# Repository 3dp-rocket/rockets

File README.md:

# 3D Printed Rockets
The goal of this project is to collaborate on designs of rockets and rocket components for 3D printing.

The first set of designs were developed in [OpenSCAD](https://www.openscad.org/). Using OpenSCAD requires some basic programming skills and it is helpful to have some knowledge of basic math and trigonometry. That said, it is easier to work with existing designs, make tweaks and assemble them into new rockets without knowing any math.

People are encourged to join and add designs they made with other tools. As we learn more togther we will figure out the best tools to use for different projects and skills. 

We want rocket designs to be safe and sound and to follow standard rocket design rules. So we also encourgae contributors to provide documentation about how parts were stress tested and OpenRocket model/simulation results as well as real field test results.

You will find common parts under the 'parts' folder and the first rocket design in this project under 'Janus'. Feel free to add new designs or new parts you have been devloping. Make sure to add a header to your files with you name to get propper attribution. 

To join this project please create an [issue](https://github.com/3dp-rocket/rockets/issues) and type access request in the description. 

Janus - HM115 DM - Tri-Cities - Swoosh - 2019

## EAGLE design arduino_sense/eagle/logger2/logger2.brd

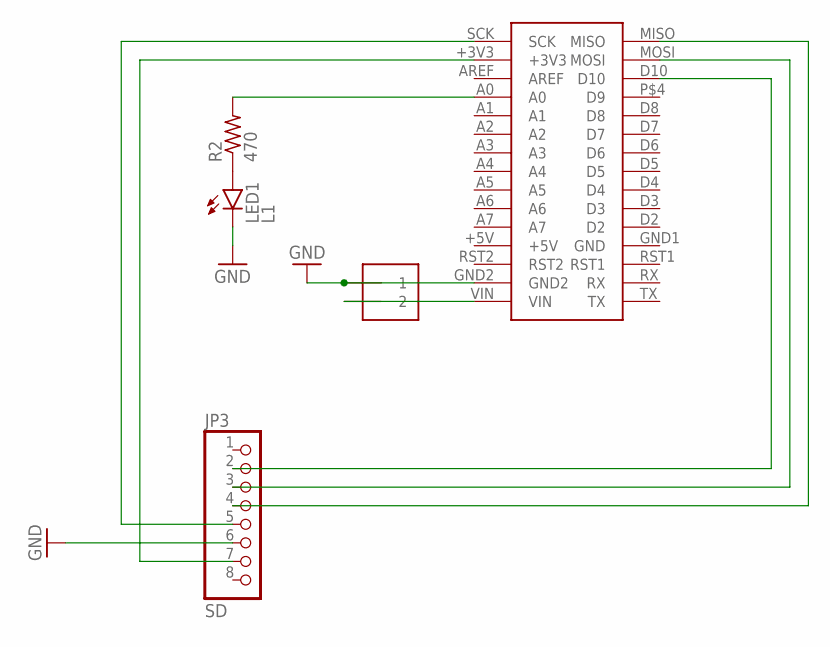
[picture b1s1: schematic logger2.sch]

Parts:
J1: 1X2-3.5MM
JP3: SD; 1X08-BIG
LED1: L1; SFH482
MC1: NANODEVICE; NANO
R2: 470; V526-0

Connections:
GND: J1.1, JP3.6, LED1.K (C), MC1.GND2
unnamed: JP3.5, MC1.SCK
unnamed: JP3.7, MC1.+3V3
unnamed: J1.2, MC1.VIN
unnamed: JP3.3, MC1.MOSI
unnamed: JP3.4, MC1.MISO
unnamed: LED1.A, R2.1
unnamed: JP3.2, MC1.D10
unnamed: MC1.A0, R2.2

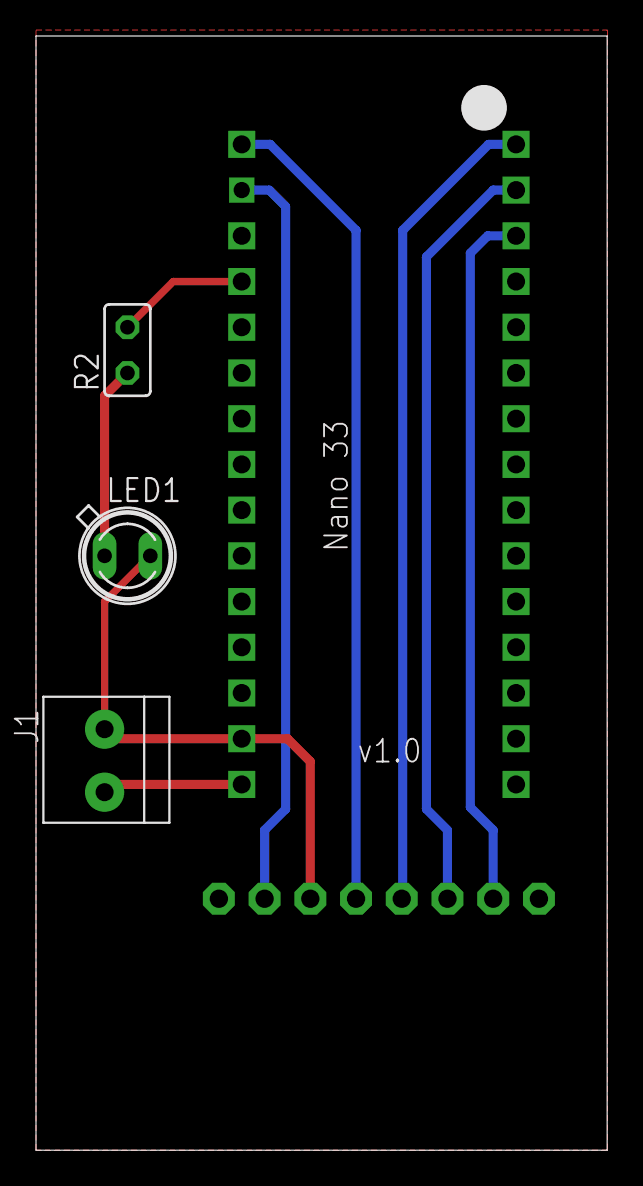
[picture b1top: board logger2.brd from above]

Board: 2 copper layers, 31.7 x 61.9 mm, 5 parts (1 on the bottom side), 9 nets.

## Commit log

2019-05-30 created nose.scad
2019-05-31 created
2019-06-01 janus
2019-06-01 added retainer and lugs
2019-06-01 added janus picture
2019-06-07 added open rocket model
2019-06-13 ellipsoid fin
2019-06-13 thicker fin
2019-06-13 changed fin cord length
2019-06-13 fins
2019-06-15 fixed ring height
2019-09-15 new piston, ejection charge test device
2019-09-29 updated piston
2019-09-29 new build scripts
2019-12-21 preparing to test rocket with 54mm motor
2019-12-21 adding build scripts
2020-01-11 changed threading library to OpenSCAD std library
2020-01-11 updated stl's
2020-01-12 changed motor retainer thread size
2020-01-20 fix fin support gap in motor tube
2020-01-20 track *.stl files using git lfs
2020-01-20 udpated stls
2020-01-23 new ejection charge holder for static tests
2020-01-29 added distance table
2020-03-20 added data logger arduino sense sketch
2020-03-20 removed stl due to github limit
